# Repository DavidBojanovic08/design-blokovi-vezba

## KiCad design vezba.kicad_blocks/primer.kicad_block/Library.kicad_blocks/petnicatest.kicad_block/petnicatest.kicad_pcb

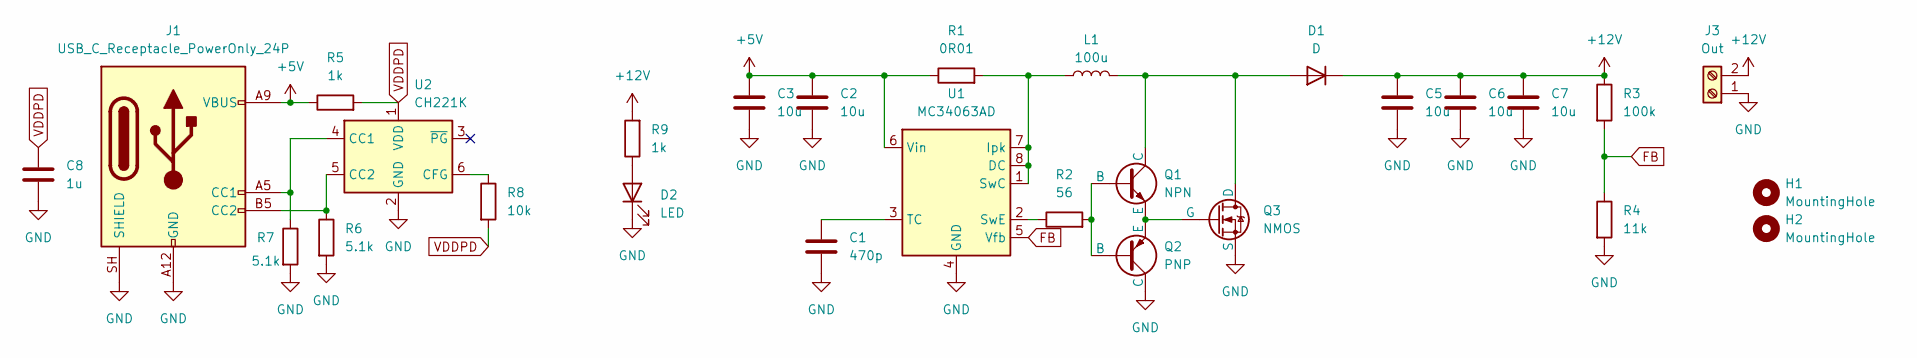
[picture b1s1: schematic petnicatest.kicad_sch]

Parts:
C1: 470p; C_0603_1608Metric
C2, C3, C5, C6, C7: 10u; C_0805_2012Metric
C8: 1u; C_0603_1608Metric
D1: D; D_0603_1608Metric
D2: LED; LED_0603_1608Metric
H1, H2: MountingHole; MountingHole_2.1mm
J1: USB_C_Receptacle_PowerOnly_24P; USB_C_Receptacle_GCT_USB4105-xx-A_16P_TopMnt_Horizontal
J3: Out; TerminalBlock_MetzConnect_Type059_RT06302HBWC_1x02_P3.50mm_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
L1: 100u; L_Neosid_SMS-ME3015
Q1: NPN; SOT-23-3
Q2: PNP; SOT-23-3
Q3: NMOS; SOT-23-3
R1: 0R01; R_2512_6332Metric
R2: 56; R_0603_1608Metric
R3: 100k; R_0603_1608Metric
R4: 11k; R_0603_1608Metric
R5, R9: 1k; R_0603_1608Metric
R6, R7: 5.1k; R_0603_1608Metric
R8: 10k; R_0603_1608Metric
U1: MC34063AD; SOIC-8_3.9x4.9mm_P1.27mm
U2: CH221K; SOT-23-6

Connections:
+5V: C2.1, C3.1, J1.A4 (VBUS), J1.A9 (VBUS), J1.B4 (VBUS), J1.B9 (VBUS), R1.1, R5.1, U1.6 (Vin)
+12V: C5.1, C6.1, C7.1, D1.1 (K), J3.2, R3.1, R9.2
FB: R3.2, R4.1, U1.5 (Vfb)
GND: C1.2, C2.2, C3.2, C5.2, C6.2, C7.2, C8.1, D2.1 (K), J1.A1 (GND), J1.A12 (GND), J1.B1 (GND), J1.B12 (GND), J1.SH (SHIELD), J3.1, Q2.1 (C), Q3.3 (S), R4.2, R6.2, R7.2, U1.4 (GND), U2.2 (GND)
unnamed: D1.2 (A), L1.2, Q1.1 (C), Q3.1 (D)
unnamed: D2.2 (A), R9.1
unnamed: J1.A5 (CC1), R7.1, U2.4 (CC1)
unnamed: J1.B5 (CC2), R6.1, U2.5 (CC2)
unnamed: Q1.2 (B), Q2.2 (B), R2.2
unnamed: Q1.3 (E), Q2.3 (E), Q3.2 (G)
unnamed: L1.1, R1.2, U1.1 (SwC), U1.7 (Ipk), U1.8 (DC)
unnamed: R2.1, U1.2 (SwE)
unnamed: C1.1, U1.3 (TC)
unnamed: R8.1, U2.6 (CFG)
VDDPD: C8.2, R5.2, R8.2, U2.1 (VDD)

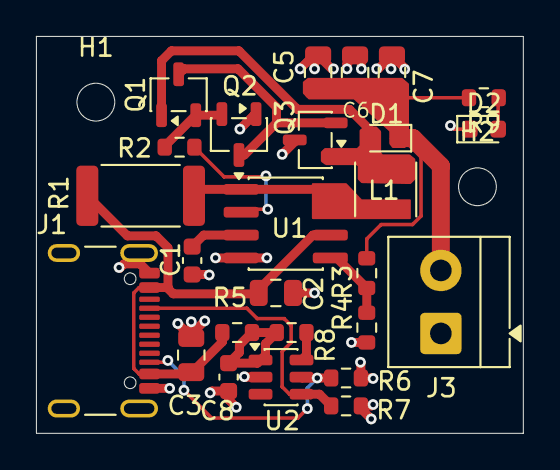
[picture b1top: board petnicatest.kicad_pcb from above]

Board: 2 copper layers, 27.0 x 22.0 mm, 28 parts (0 on the bottom side), 15 nets.
